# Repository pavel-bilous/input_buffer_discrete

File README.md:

# Discrete design for the input buffer with low THD

Impedance matching buffer. Made in KiCAD 5.

## PCB rendered in 3d:

## Schematics:

Low pass input filters capacitors are C0G multilayer ceramic. 
Decoupling capacitors are X7R 100nF or higher (1uF - 10uF will work great).

## PCB layout:

Bottom layer is GND. Top layer is signal + power and GND poured in between. Stiching vias are then applied to connect bottom and top GND planes to ensure those are as close to 0 as possible.

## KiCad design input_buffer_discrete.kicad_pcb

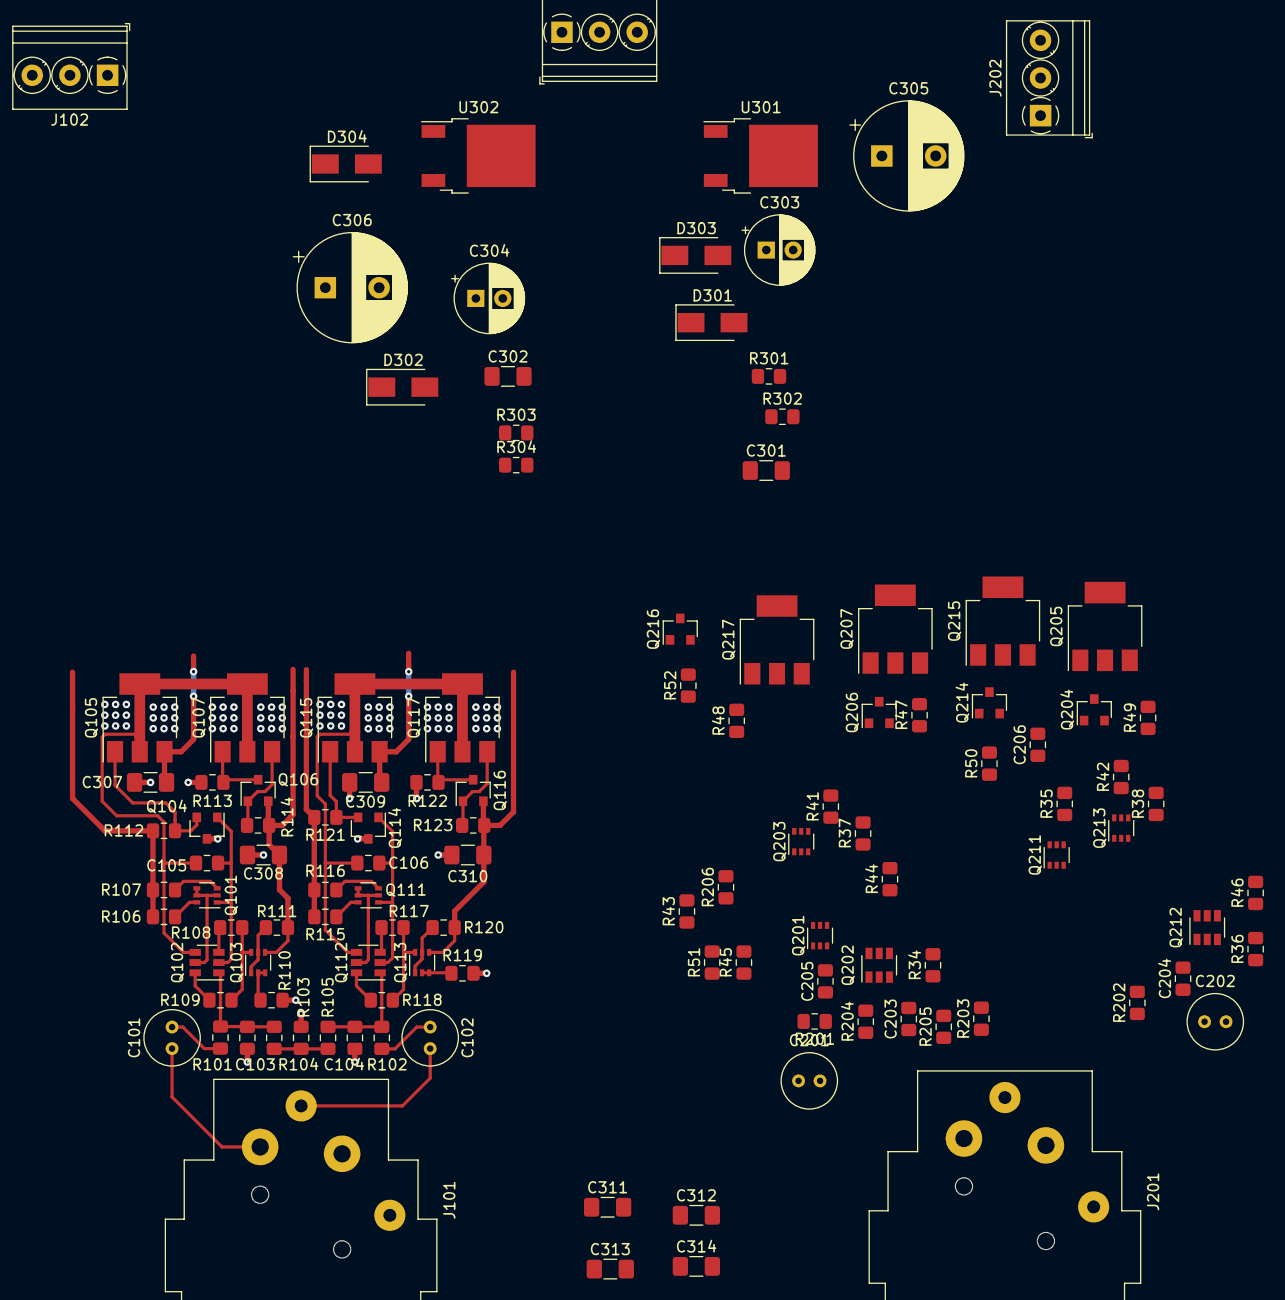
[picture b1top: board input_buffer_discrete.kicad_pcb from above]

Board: 2 copper layers, 115 parts (0 on the bottom side), 73 nets.

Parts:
C101, C102, C201, C202: 10u; C_Radial_D5.0mm_H7.0mm_P2.00mm
C103, C104, C203, C204: 100p; C_0805_2012Metric_Pad1.15x1.40mm_HandSolder
C105, C106, C205, C206: 27p; C_0805_2012Metric_Pad1.15x1.40mm_HandSolder
C301, C302, C307, C308, C309, C310, C311, C312, C313, C314: 100n; C_1206_3216Metric_Pad1.42x1.75mm_HandSolder
C303, C304: 47uF; CP_Radial_D6.3mm_P2.50mm
C305, C306: 470uF; CP_Radial_D10.0mm_P5.00mm
D301, D302, D303, D304: M7; D_SMA
J101: CH1; Jack_XLR_Neutrik_NC3FAAH2_Horizontal
J102: CH1OUT; TerminalBlock_Phoenix_PT-1,5-3-3.5-H_1x03_P3.50mm_Horizontal
J201: CH2; Jack_XLR_Neutrik_NC3FAAH2_Horizontal
J202: CH2OUT; TerminalBlock_Phoenix_PT-1,5-3-3.5-H_1x03_P3.50mm_Horizontal
J301: POWER; TerminalBlock_Phoenix_PT-1,5-3-3.5-H_1x03_P3.50mm_Horizontal
Q101, Q111, Q201, Q211: BC856BDW1; SOT-363_SC-70-6
Q102, Q112, Q202, Q212: LS844; SOT-23-6
Q103, Q113, Q203, Q213: BC846BDW1; SOT-363_SC-70-6
Q104, Q114, Q204, Q214: BC856; SOT-23
Q105, Q115, Q205, Q215: BCP53; SOT-223-3_TabPin2
Q106, Q116, Q206, Q216: BC846; SOT-23
Q107, Q117, Q207, Q217: BCP56; SOT-223-3_TabPin2
R34, R35, R36, R43, R44, R45, R46, R101, R102, R106, R107, R108, R109, R115, R116, R117, R118, R201, R202, R206: 100R; R_0805_2012Metric_Pad1.15x1.40mm_HandSolder
R37, R38, R47, R48, R110, R113, R119, R122: 5K6; R_0805_2012Metric_Pad1.15x1.40mm_HandSolder
R41, R42, R111, R120: 330R; R_0805_2012Metric_Pad1.15x1.40mm_HandSolder
R49, R50, R112, R121: 470R; R_0805_2012Metric_Pad1.15x1.40mm_HandSolder
R51, R52, R114, R123: 22R; R_0805_2012Metric_Pad1.15x1.40mm_HandSolder
R103, R203: 2M2; R_0805_2012Metric_Pad1.15x1.40mm_HandSolder
R104, R105, R204, R205: 47K; R_0805_2012Metric_Pad1.15x1.40mm_HandSolder
R301, R304: 120R; R_0805_2012Metric_Pad1.15x1.40mm_HandSolder
R302, R303: 1K4; R_0805_2012Metric_Pad1.15x1.40mm_HandSolder
U301: LM317_TO-252; TO-252-2
U302: LM337_TO252; TO-252-2

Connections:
+15V: C305.1, C307.1, C309.1, C311.1, C313.1, D301.2, D303.1, Q105.3, Q115.3, Q205.3, Q215.3, R35.2, R43.2, R45.2, R49.2, R50.2, R106.2, R107.2, R112.2, R115.2, R116.2, R121.2, R206.2, R301.1, U301.2
-15V: C306.2, C308.2, C310.2, C312.2, C314.2, D302.1, D304.2, Q103.4, Q106.2, Q113.4, Q116.2, Q203.4, Q206.2, Q213.4, Q216.2, R41.1, R42.1, R51.1, R52.1, R111.1, R114.1, R120.1, R123.1, R304.2, U302.3
/ch1/CH1+_FB: C105.2, Q101.1, Q102.2, Q104.1
/ch1/CH1-_FB: C106.2, Q111.1, Q112.2, Q114.1
/ch1/CH1IN+: C103.1, Q102.1, R101.1, R104.2
/ch1/CH1IN-: C104.2, Q112.1, R102.1, R105.1
/ch2/CH2+_FB: C205.2, Q201.1, Q202.2, Q204.1
/ch2/CH2-_FB: C206.2, Q211.1, Q212.2, Q214.1
/ch2/CH2IN+: C203.1, Q202.1, R201.1, R204.2
/ch2/CH2IN-: C204.2, Q212.1, R202.1, R205.1
/psu/317ADJ: C303.1, D303.2, R301.2, R302.1, U301.1
/psu/337ADJ: C304.2, D304.1, R303.2, R304.1, U302.1
/psu/V+: C301.1, D301.1, J301.1, U301.3
/psu/V-: C302.2, D302.2, J301.3, U302.2
CH1OUT+: C105.1, J102.2, Q102.4, Q105.2, Q107.2
CH1OUT-: C106.1, J102.3, Q112.4, Q115.2, Q117.2
CH2OUT+: C205.1, J202.2, Q202.4, Q205.2, Q207.2
CH2OUT-: C206.1, J202.3, Q212.4, Q215.2, Q217.2
GND: C103.2, C104.1, C203.2, C204.1, C301.2, C302.1, C303.2, C304.1, C305.2, C306.1, C307.2, C308.1, C309.2, C310.1, C311.2, C312.1, C313.2, C314.1, J101.1, J101.G, J102.1, J201.1, J201.G, J202.1, J301.2, Q104.3, Q114.3, Q204.3, Q214.3, R37.2, R38.2, R47.2, R48.2, R103.2, R110.2, R113.2, R119.2, R122.2, R203.2, R302.2, R303.1
unnamed: C101.1, R101.2
unnamed: C101.2, J101.2
unnamed: C102.1, R102.2
unnamed: C102.2, J101.3
unnamed: C201.1, R201.2
unnamed: C201.2, J201.2
unnamed: C202.1, R202.2
unnamed: C202.2, J201.3
unnamed: Q101.2, Q101.4, Q101.5, Q102.5
unnamed: Q101.3, R107.1
unnamed: Q101.6, R106.1
unnamed: Q102.3, R108.2
unnamed: Q102.6, R109.2
unnamed: Q103.1, Q103.5, R111.2
unnamed: Q103.2, Q103.3, R110.1
unnamed: Q103.6, R108.1, R109.1
unnamed: Q104.2, Q105.1, R112.1
unnamed: Q106.1, Q107.3, R114.2
unnamed: Q106.3, Q107.1, R113.1
unnamed: Q111.2, Q111.4, Q111.5, Q112.5
unnamed: Q111.3, R116.1
unnamed: Q111.6, R115.1
unnamed: Q112.3, R117.2
unnamed: Q112.6, R118.2
unnamed: Q113.1, Q113.5, R120.2
unnamed: Q113.2, Q113.3, R119.1
unnamed: Q113.6, R117.1, R118.1
unnamed: Q114.2, Q115.1, R121.1
unnamed: Q116.1, Q117.3, R123.2
unnamed: Q116.3, Q117.1, R122.1
unnamed: Q201.2, Q201.4, Q201.5, Q202.5
unnamed: Q201.3, R43.1
unnamed: Q201.6, R206.1
unnamed: Q202.3, R34.2
unnamed: Q202.6, R44.2
unnamed: Q203.1, Q203.5, R41.2
unnamed: Q203.2, Q203.3, R37.1
unnamed: Q203.6, R34.1, R44.1
unnamed: Q204.2, Q205.1, R49.1
unnamed: Q206.1, Q207.3, R51.2
unnamed: Q206.3, Q207.1, R47.1
unnamed: Q211.2, Q211.4, Q211.5, Q212.5
unnamed: Q211.3, R45.1
unnamed: Q211.6, R35.1
unnamed: Q212.3, R36.2
unnamed: Q212.6, R46.2
unnamed: Q213.1, Q213.5, R42.2
unnamed: Q213.2, Q213.3, R38.1
unnamed: Q213.6, R36.1, R46.1
unnamed: Q214.2, Q215.1, R50.1
unnamed: Q216.1, Q217.3, R52.2
unnamed: Q216.3, Q217.1, R48.1
unnamed: R103.1, R104.1, R105.2
unnamed: R203.1, R204.1, R205.2

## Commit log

2023-05-24 added pages and buffer schematics
2023-05-24 ch1 and ch2 are complete
2023-05-29 assigned footprints
2023-05-29 started pcb layout
2023-05-30 pcb started
2023-05-31 pcb layout
2023-06-03 minor changes
